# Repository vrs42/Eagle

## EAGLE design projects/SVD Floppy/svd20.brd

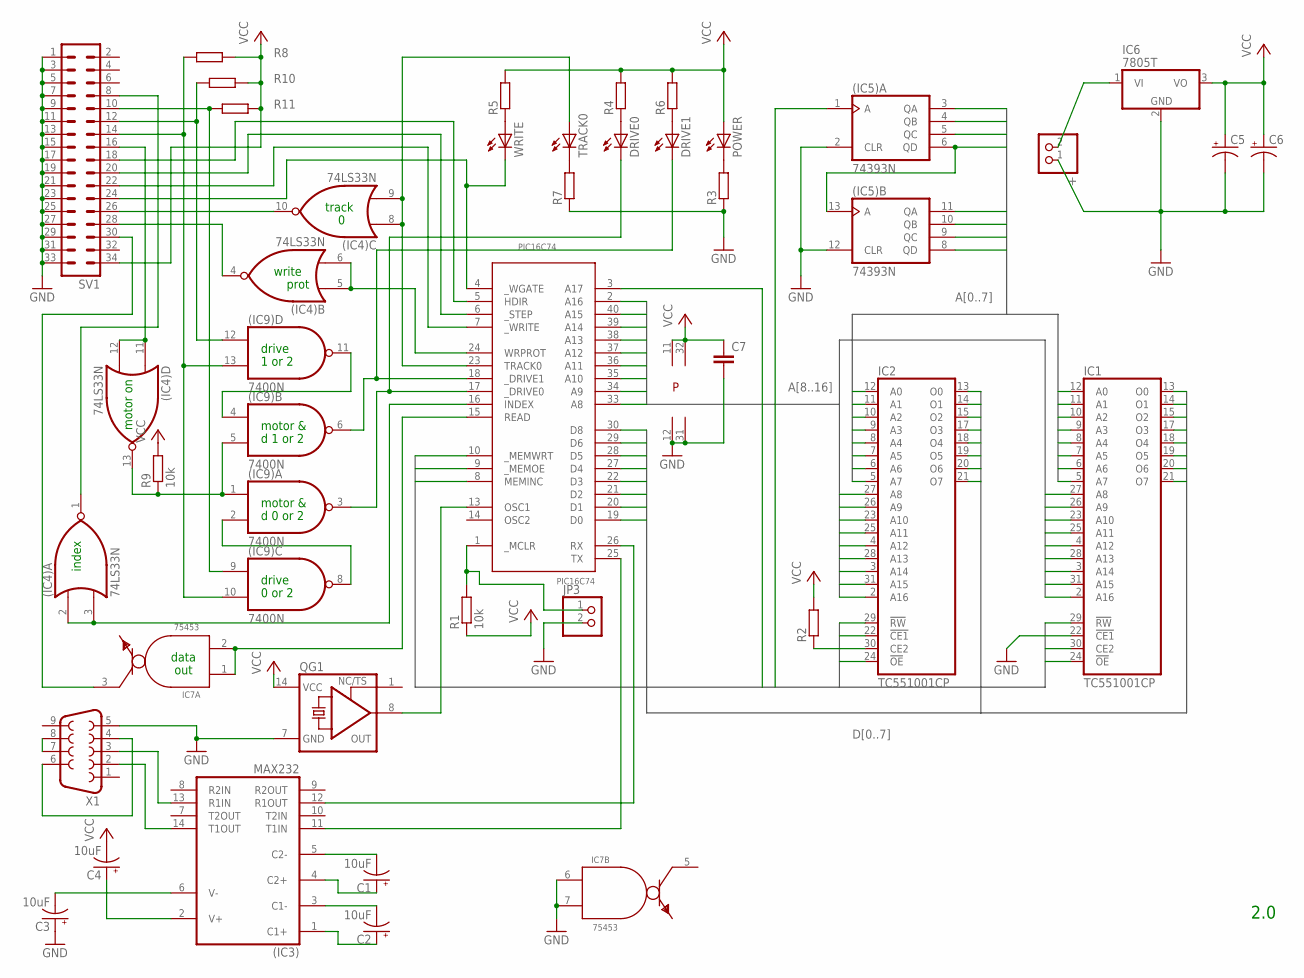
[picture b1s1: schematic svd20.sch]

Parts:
(IC3): MAX232; DIL16
(IC4): 74LS33N; DIL14
(IC5): 74393N; DIL14
(IC9): 7400N; DIL14
+: PINHD-1X2; 1X02
C1, C2, C3, C4: 10uF; E2-5
C5, C6: CPOL-USE2-5; E2-5
C7: C2,5-3; C2.5-3
DRIVE0, DRIVE1: LED3MM
IC1, IC2: TC551001CP; DIL32
IC6: 7805T; TO220H
IC7: 75453; DIL08
JP3: PINHD-1X2; 1X02
PIC16C74: PIC16C74; DIL40
POWER: LED3MM
QG1: XO-14; DIL14S
R1, R9: 10k; 0204/5
R2, R3, R4, R5, R6, R7, R8, R10, R11: R-EU_0204/5; 0204/5
SV1: ML34
TRACK0: LED3MM
WRITE: LED3MM
X1: F09HP

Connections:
!OE: IC1.24 (!OE), IC2.24 (!OE), PIC16C74.9 (_MEMOE)
!WE: IC1.29 (!RW), IC2.29 (!RW), PIC16C74.10 (_MEMWRT)
A0: (IC5).3 (QA), IC1.12 (A0), IC2.12 (A0)
A1: (IC5).4 (QB), IC1.11 (A1), IC2.11 (A1)
A2: (IC5).5 (QC), IC1.10 (A2), IC2.10 (A2)
A3: (IC5).6 (QD), (IC5).13 (A), IC1.9 (A3), IC2.9 (A3)
A4: (IC5).11 (QA), IC1.8 (A4), IC2.8 (A4)
A5: (IC5).10 (QB), IC1.7 (A5), IC2.7 (A5)
A6: (IC5).9 (QC), IC1.6 (A6), IC2.6 (A6)
A7: (IC5).8 (QD), IC1.5 (A7), IC2.5 (A7)
A8: IC1.27 (A8), IC2.27 (A8), PIC16C74.33 (A8)
A9: IC1.26 (A9), IC2.26 (A9), PIC16C74.34 (A9)
A10: IC1.23 (A10), IC2.23 (A10), PIC16C74.35 (A10)
A11: IC1.25 (A11), IC2.25 (A11), PIC16C74.36 (A11)
A12: IC1.4 (A12), IC2.4 (A12), PIC16C74.37 (A12)
A13: IC1.28 (A13), IC2.28 (A13), PIC16C74.38 (A13)
A14: IC1.3 (A14), IC2.3 (A14), PIC16C74.39 (A14)
A15: IC1.31 (A15), IC2.31 (A15), PIC16C74.40 (A15)
A16: IC1.2 (A16), IC2.2 (A16), PIC16C74.2 (A16)
A17: IC1.30 (CE2), IC2.22 (!CE1), PIC16C74.3 (A17)
CLK: (IC5).1 (A), PIC16C74.8 (MEMINC)
D0: IC1.13 (O0), IC2.13 (O0), PIC16C74.19 (D0)
D1: IC1.14 (O1), IC2.14 (O1), PIC16C74.20 (D1)
D2: IC1.15 (O2), IC2.15 (O2), PIC16C74.21 (D2)
D3: IC1.17 (O3), IC2.17 (O3), PIC16C74.22 (D3)
D4: IC1.18 (O4), IC2.18 (O4), PIC16C74.27 (D4)
D5: IC1.19 (O5), IC2.19 (O5), PIC16C74.28 (D5)
D6: IC1.20 (O6), IC2.20 (O6), PIC16C74.29 (D6)
D7: IC1.21 (O7), IC2.21 (O7), PIC16C74.30 (D8)
GND: (IC3).15 (GND), (IC4).7 (GND), (IC5).2 (CLR), (IC5).7 (GND), (IC5).12 (CLR), (IC9).7 (GND), +.1, C3.+, C5.-, C6.-, C7.2, IC1.16 (GND), IC1.22 (!CE1), IC2.16 (GND), IC6.2 (GND), IC7.4 (GND), IC7.6 (I0), IC7.7 (I1), JP3.2, PIC16C74.12 (GND), PIC16C74.31 (GND), QG1.7 (GND), R3.1, R7.1, SV1.1, SV1.3, SV1.5, SV1.7, SV1.9, SV1.11, SV1.13, SV1.15, SV1.17, SV1.19, SV1.21, SV1.23, SV1.25, SV1.27, SV1.29, SV1.31, SV1.33, X1.5
unnamed: IC2.30 (CE2), R2.1
unnamed: JP3.1, PIC16C74.1 (_MCLR), R1.2
unnamed: (IC3).1 (C1+), C2.+
unnamed: (IC3).3 (C1-), C2.-
unnamed: (IC3).4 (C2+), C1.+
unnamed: (IC3).5 (C2-), C1.-
unnamed: (IC3).2 (V+), C4.+
unnamed: PIC16C74.13 (OSC1), QG1.8 (OUT)
unnamed: (IC3).12 (R1OUT), PIC16C74.26 (RX)
unnamed: (IC9).6 (O), DRIVE1.K (C), PIC16C74.18 (_DRIVE1)
unnamed: (IC4).11 (I0), (IC4).12 (I1), SV1.16
unnamed: (IC9).12 (I0), R10.1, SV1.12
unnamed: (IC4).13 (O), (IC9).1 (I0), (IC9).5 (I1), R9.1
unnamed: (IC4).1 (O), SV1.8
unnamed: PIC16C74.4 (_WGATE), SV1.24, WRITE.K (C)
unnamed: PIC16C74.7 (_WRITE), SV1.22
unnamed: (IC4).10 (O), SV1.26
unnamed: X1.7, X1.8
unnamed: IC7.1 (I0), IC7.2 (I1), PIC16C74.15 (READ)
unnamed: (IC9).4 (I0), (IC9).11 (O)
unnamed: (IC4).8 (I0), (IC4).9 (I1), PIC16C74.23 (TRACK0), TRACK0.A
unnamed: (IC9).3 (O), DRIVE0.K (C), PIC16C74.17 (_DRIVE0)
unnamed: (IC3).11 (T1IN), PIC16C74.25 (TX)
unnamed: (IC3).13 (R1IN), X1.3
unnamed: X1.4, X1.6
unnamed: (IC3).14 (T1OUT), X1.2
unnamed: (IC3).6 (V-), C3.-
unnamed: (IC4).2 (I0), (IC4).3 (I1), PIC16C74.16 (INDEX)
unnamed: +.2, IC6.1 (VI)
unnamed: POWER.K (C), R3.2
unnamed: DRIVE0.A, R4.1
unnamed: DRIVE1.A, R6.1
unnamed: R5.1, WRITE.A
unnamed: R7.2, TRACK0.K (C)
unnamed: IC7.3 (O), SV1.30
unnamed: (IC4).5 (I0), (IC4).6 (I1), PIC16C74.24 (WRPROT)
unnamed: (IC9).9 (I0), R11.1, SV1.10
unnamed: (IC9).2 (I1), (IC9).8 (O)
unnamed: (IC4).4 (O), SV1.28
unnamed: PIC16C74.6 (_STEP), SV1.20
unnamed: PIC16C74.5 (HDIR), SV1.18
unnamed: (IC9).10 (I1), (IC9).13 (I1), R8.1, SV1.14
VCC: (IC3).16 (VCC), (IC4).14 (VCC), (IC5).14 (VCC), (IC9).14 (VCC), C4.-, C5.+, C6.+, C7.1, IC1.32 (VCC), IC2.32 (VCC), IC6.3 (VO), IC7.8 (VCC), PIC16C74.11 (VCC), PIC16C74.32 (VCC), POWER.A, QG1.14 (VCC), R1.1, R2.2, R4.2, R5.2, R6.2, R8.2, R9.2, R10.2, R11.2, SV1.34

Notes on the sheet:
2.0
motor on
index
data
out
write
prot
track
drive
motor &
1 or 2
d 1 or 2
d 0 or 2
0 or 2

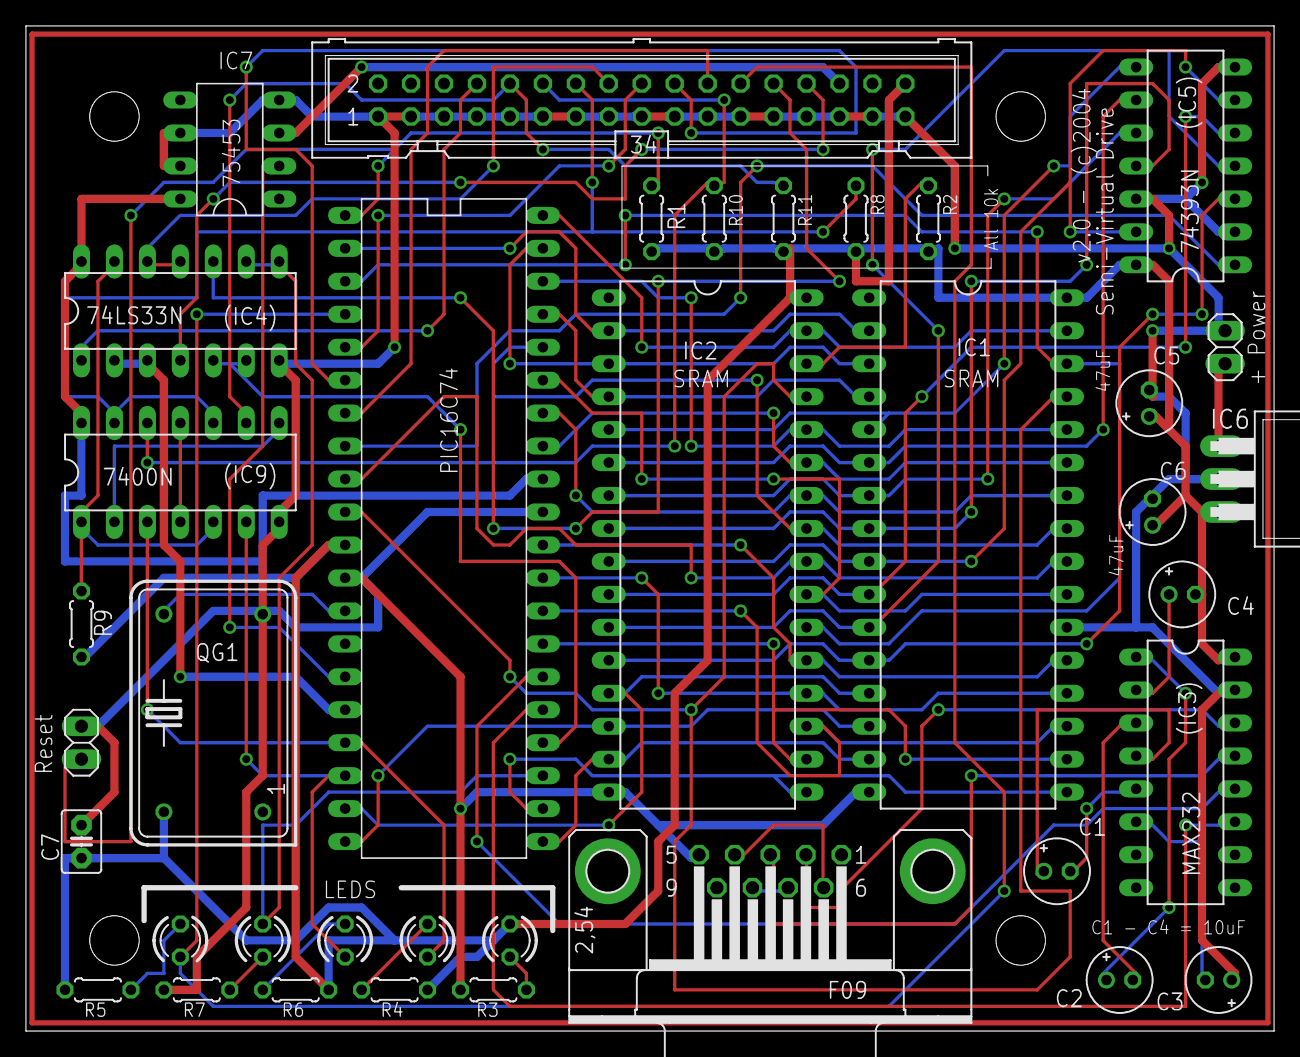
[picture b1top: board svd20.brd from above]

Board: 2 copper layers, 96.2 x 77.5 mm, 37 parts (0 on the bottom side), 73 nets.

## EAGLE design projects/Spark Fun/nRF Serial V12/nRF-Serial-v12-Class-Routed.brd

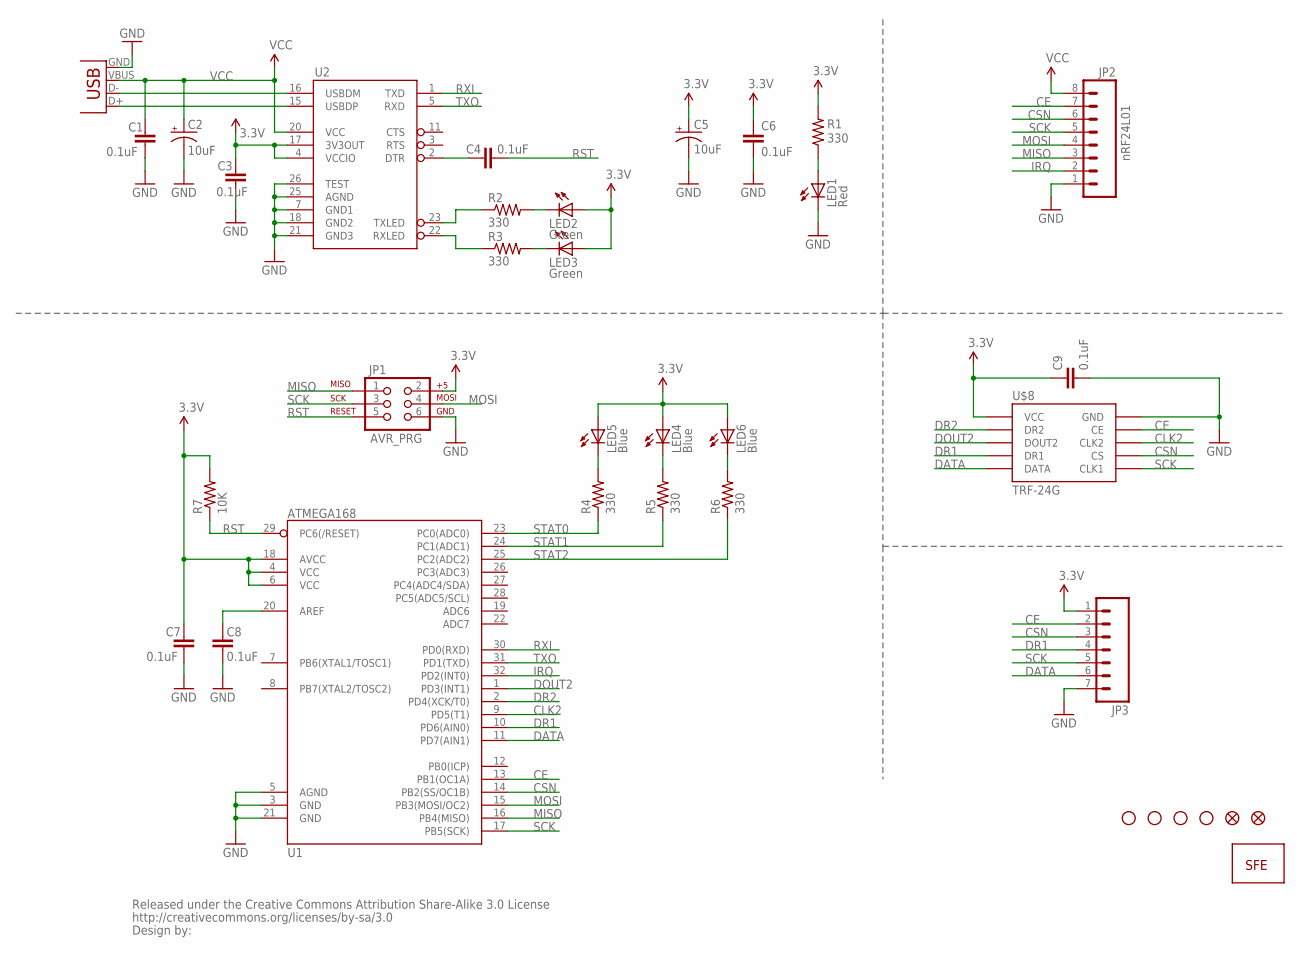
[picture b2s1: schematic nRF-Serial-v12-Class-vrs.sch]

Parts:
C1, C3, C4, C6, C7, C8, C9: 0.1uF; C0402
C2, C5: 10uF; EIA3216
JP1: AVR_PRG; 2X3
JP2: nRF24L01; 1X08
JP3: M07; 1X07
LED1: Red; LED-0603
LED2, LED3: Green; LED-0603
LED4, LED5, LED6: Blue; LED-0603
R1, R2, R3, R4, R5, R6: 330; C0402
R7: 10K; C0402
U1: ATMEGA168; TQFP32-08
U2: FT232RL-BASICSSOP; SSOP28DB
U$1: LOGO-SFENEW; SFE-NEW-WEBLOGO
U$2, U$3: FIDUCIAL1X2; FIDUCIAL-1X2
U$4, U$5, U$6, U$7: STAND-OFF
U$8: TRF-24G; TRF-24G-SOCKET
U$9: CREATIVE_COMMONS
X1: USBSMD; USB-MINIB

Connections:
3.3V: C3.1, C5.A (+), C6.1, C7.1, C9.1, JP1.2, JP3.1, LED2.A, LED3.A, LED4.A, LED5.A, LED6.A, R1.2, R7.2, U1.4 (VCC), U1.6 (VCC), U1.18 (AVCC), U2.4 (VCCIO), U2.17 (3V3OUT), U$8.P$1 (VCC)
CE: JP2.7, JP3.2, U1.13 (PB1(OC1A)), U$8.P$9 (CE)
CLK2: U1.9 (PD5(T1)), U$8.P$8 (CLK2)
CSN: JP2.6, JP3.3, U1.14 (PB2(SS/OC1B)), U$8.P$7 (CS)
DATA: JP3.6, U1.11 (PD7(AIN1)), U$8.P$5 (DATA)
DOUT2: U1.1 (PD3(INT1)), U$8.P$3 (DOUT2)
DR1: JP3.4, U1.10 (PD6(AIN0)), U$8.P$4 (DR1)
DR2: U1.2 (PD4(XCK/T0)), U$8.P$2 (DR2)
GND: C1.2, C2.C (-), C3.2, C5.C (-), C6.2, C7.2, C8.1, C9.2, JP1.6, JP2.1, JP3.7, LED1.C, U1.3 (GND), U1.5 (AGND), U1.21 (GND), U2.7 (GND1), U2.18 (GND2), U2.21 (GND3), U2.25 (AGND), U2.26 (TEST), U$8.P$10 (GND), X1.GND
IRQ: JP2.2, U1.32 (PD2(INT0))
MISO: JP1.1, JP2.3, U1.16 (PB4(MISO))
MOSI: JP1.4, JP2.4, U1.15 (PB3(MOSI/OC2))
unnamed: C8.2, U1.20 (AREF)
unnamed: C4.2, U2.2 (DTR)
unnamed: R2.1, U2.23 (TXLED)
unnamed: R3.1, U2.22 (RXLED)
unnamed: LED3.C, R3.2
unnamed: LED2.C, R2.2
unnamed: LED5.C, R4.2
unnamed: LED4.C, R5.2
unnamed: LED6.C, R6.2
unnamed: LED1.A, R1.1
unnamed: U2.16 (USBDM), X1.D-
unnamed: U2.15 (USBDP), X1.D+
RST: C4.1, JP1.5, R7.1, U1.29 (PC6(/RESET))
RXI: U1.30 (PD0(RXD)), U2.1 (TXD)
SCK: JP1.3, JP2.5, JP3.5, U1.17 (PB5(SCK)), U$8.P$6 (CLK1)
STAT0: R4.1, U1.23 (PC0(ADC0))
STAT1: R5.1, U1.24 (PC1(ADC1))
STAT2: R6.1, U1.25 (PC2(ADC2))
TXO: U1.31 (PD1(TXD)), U2.5 (RXD)
VCC: C1.1, C2.A (+), JP2.8, U2.20 (VCC), X1.VBUS

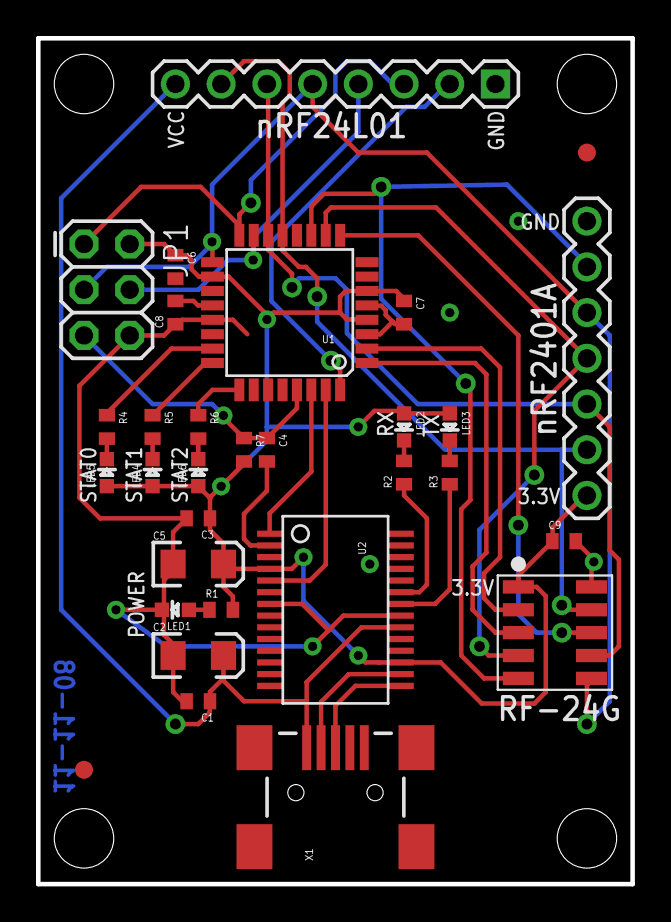
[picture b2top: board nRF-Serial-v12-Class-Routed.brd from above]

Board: 2 copper layers, 33.0 x 47.0 mm, 37 parts (1 on the bottom side), 32 nets.

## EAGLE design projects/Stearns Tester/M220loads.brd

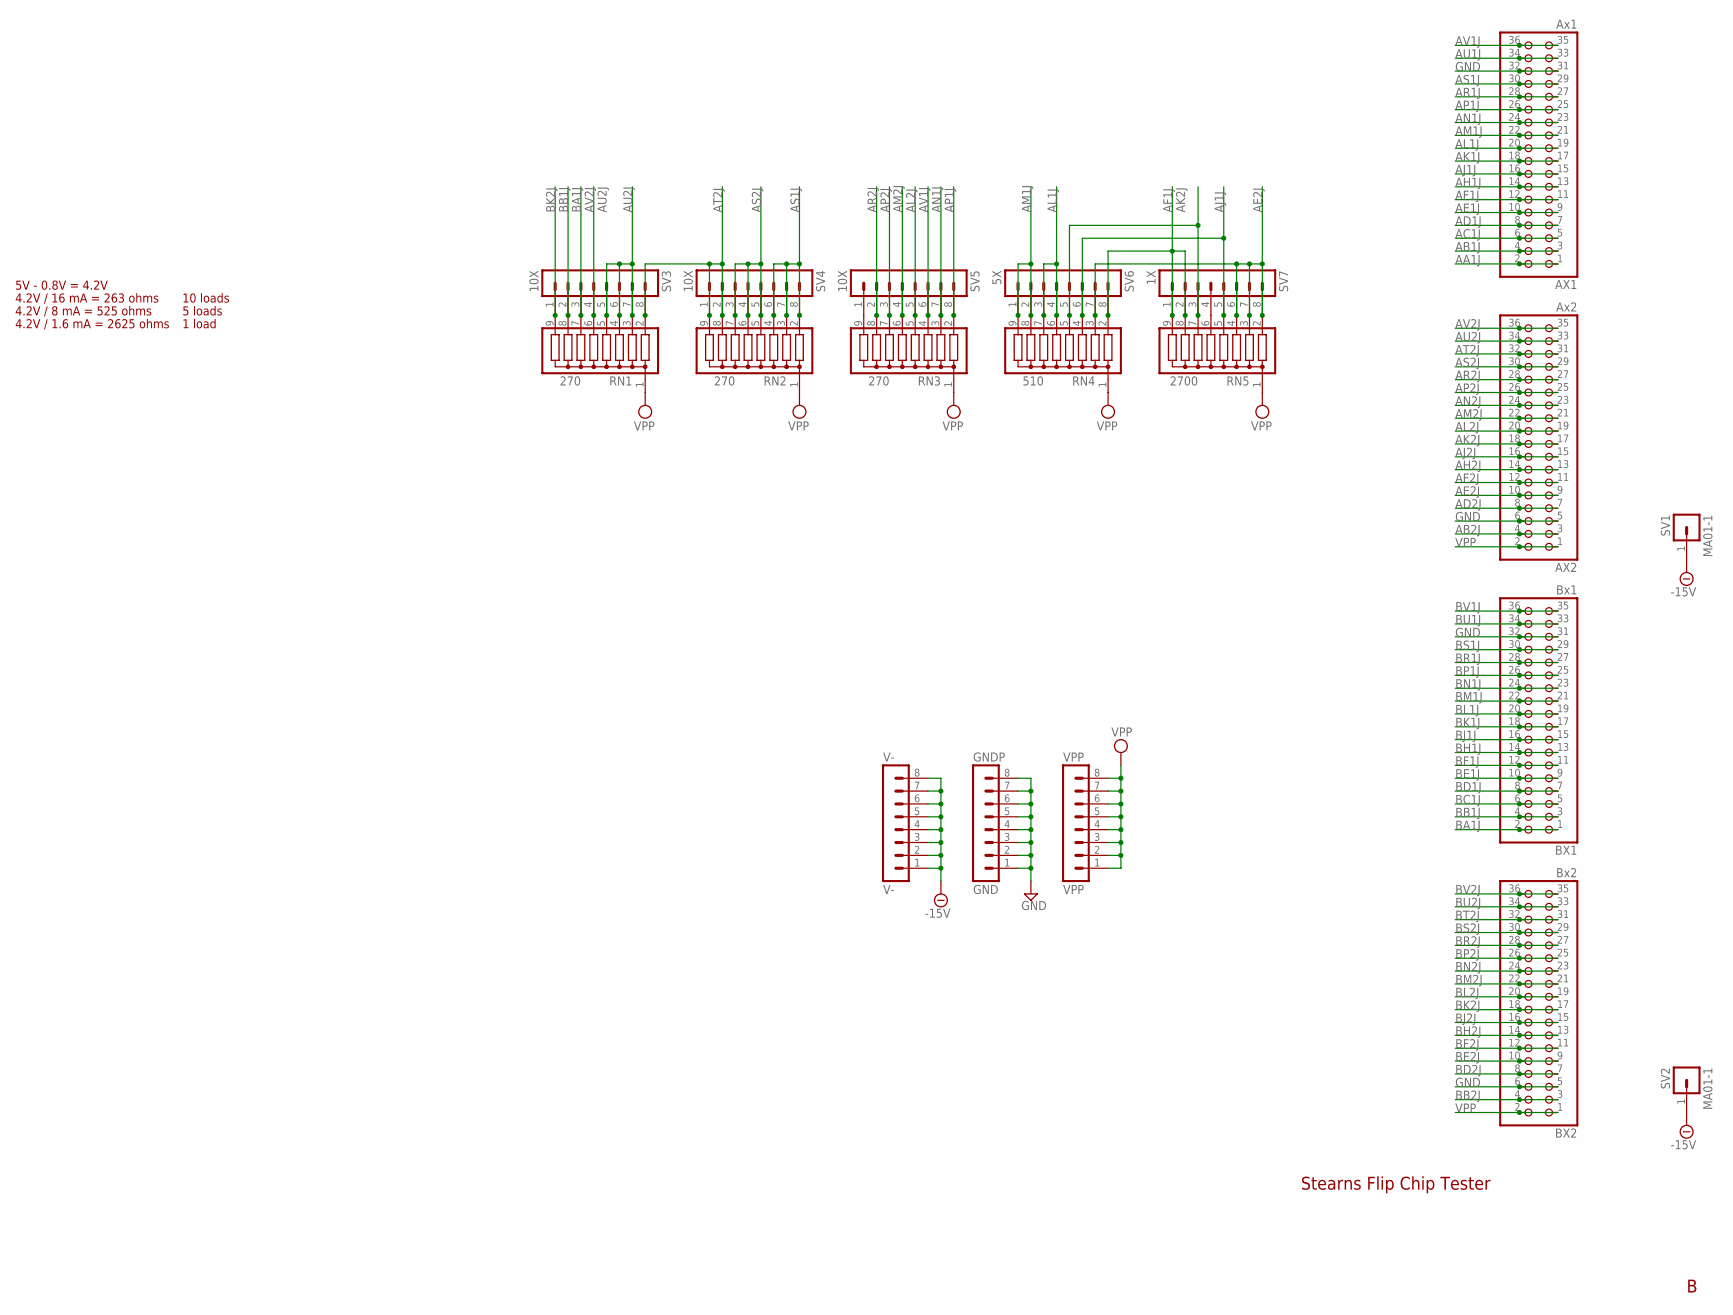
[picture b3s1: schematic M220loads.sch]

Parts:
AX1: Ax1; 2X18
AX2: Ax2; 2X18
BX1: Bx1; 2X18
BX2: Bx2; 2X18
GNDP: GND; MA08-1
RN1, RN2, RN3: 270; SIL9
RN4: 510; SIL9
RN5: 2700; SIL9
SV1, SV2: MA01-1
SV3, SV4, SV5: 10X; MA08-1
SV6: 5X; MA08-1
SV7: 1X; MA08-1
V-: V-; MA08-1
VPP: VPP; MA08-1

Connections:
-15V: SV1.1, SV2.1, V-.1, V-.2, V-.3, V-.4, V-.5, V-.6, V-.7, V-.8
AA1J: AX1.1, AX1.2
AB1J: AX1.3, AX1.4
AB2J: AX2.3, AX2.4
AC1J: AX1.5, AX1.6
AD1J: AX1.7, AX1.8
AD2J: AX2.7, AX2.8
AE1J: AX1.9, AX1.10
AE2J: AX2.9, AX2.10, RN4.3, RN5.2, RN5.3, RN5.4, SV6.7, SV7.6, SV7.7, SV7.8
AF1J: AX1.11, AX1.12, RN4.2, RN5.8, RN5.9, SV6.8, SV7.1, SV7.2
AF2J: AX2.11, AX2.12
AH1J: AX1.13, AX1.14
AH2J: AX2.13, AX2.14
AJ1J: AX1.15, AX1.16, RN4.4, RN5.5, SV6.6, SV7.5
AJ2J: AX2.15, AX2.16
AK1J: AX1.17, AX1.18
AK2J: AX2.17, AX2.18, RN4.5, RN5.7, SV6.5, SV7.3
AL1J: AX1.19, AX1.20, RN4.6, RN4.7, SV6.3, SV6.4
AL2J: AX2.19, AX2.20, RN3.5, SV5.5
AM1J: AX1.21, AX1.22, RN4.8, RN4.9, SV6.1, SV6.2
AM2J: AX2.21, AX2.22, RN3.6, SV5.4
AN1J: AX1.23, AX1.24, RN3.3, SV5.7
AN2J: AX2.23, AX2.24
AP1J: AX1.25, AX1.26, RN3.2, SV5.8
AP2J: AX2.25, AX2.26, RN3.7, SV5.3
AR1J: AX1.27, AX1.28
AR2J: AX2.27, AX2.28, RN3.8, SV5.2
AS1J: AX1.29, AX1.30, RN2.2, RN2.3, RN2.4, SV4.6, SV4.7, SV4.8
AS2J: AX2.29, AX2.30, RN2.5, RN2.6, RN2.7, SV4.3, SV4.4, SV4.5
AT2J: AX2.31, AX2.32, RN1.2, RN2.8, RN2.9, SV3.8, SV4.1, SV4.2
AU1J: AX1.33, AX1.34
AU2J: AX2.33, AX2.34, RN1.3, RN1.4, RN1.5, SV3.5, SV3.6, SV3.7
AV1J: AX1.35, AX1.36, RN3.4, SV5.6
AV2J: AX2.35, AX2.36, RN1.6, SV3.4
BA1J: BX1.1, BX1.2, RN1.7, SV3.3
BB1J: BX1.3, BX1.4, RN1.8, SV3.2
BB2J: BX2.3, BX2.4
BC1J: BX1.5, BX1.6
BD1J: BX1.7, BX1.8
BD2J: BX2.7, BX2.8
BE1J: BX1.9, BX1.10
BE2J: BX2.9, BX2.10
BF1J: BX1.11, BX1.12
BF2J: BX2.11, BX2.12
BH1J: BX1.13, BX1.14
BH2J: BX2.13, BX2.14
BJ1J: BX1.15, BX1.16
BJ2J: BX2.15, BX2.16
BK1J: BX1.17, BX1.18
BK2J: BX2.17, BX2.18, RN1.9, SV3.1
BL1J: BX1.19, BX1.20
BL2J: BX2.19, BX2.20
BM1J: BX1.21, BX1.22
BM2J: BX2.21, BX2.22
BN1J: BX1.23, BX1.24
BN2J: BX2.23, BX2.24
BP1J: BX1.25, BX1.26
BP2J: BX2.25, BX2.26
BR1J: BX1.27, BX1.28
BR2J: BX2.27, BX2.28
BS1J: BX1.29, BX1.30
BS2J: BX2.29, BX2.30
BT2J: BX2.31, BX2.32
BU1J: BX1.33, BX1.34
BU2J: BX2.33, BX2.34
BV1J: BX1.35, BX1.36
BV2J: BX2.35, BX2.36
GND: AX1.31, AX1.32, AX2.5, AX2.6, BX1.31, BX1.32, BX2.5, BX2.6, GNDP.1, GNDP.2, GNDP.3, GNDP.4, GNDP.5, GNDP.6, GNDP.7, GNDP.8
unnamed: RN3.9, SV5.1
unnamed: RN5.6, SV7.4
VPP: AX2.1, AX2.2, BX2.1, BX2.2, RN1.1, RN2.1, RN3.1, RN4.1, RN5.1, VPP.1, VPP.2, VPP.3, VPP.4, VPP.5, VPP.6, VPP.7, VPP.8

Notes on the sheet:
Stearns Flip Chip Tester
5V - 0.8V = 4.2V
4.2V / 16 mA = 263 ohms
4.2V / 8 mA = 525 ohms
4.2V / 1.6 mA = 2625 ohms
10 loads
5 loads
1 load

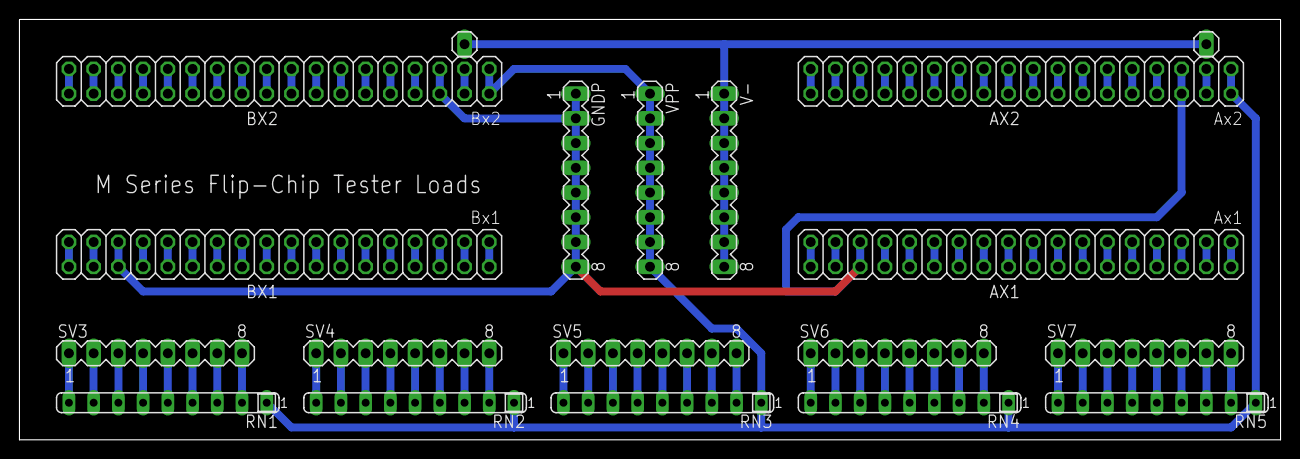
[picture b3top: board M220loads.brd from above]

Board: 4 copper layers, 129.5 x 43.2 mm, 19 parts (0 on the bottom side), 71 nets.

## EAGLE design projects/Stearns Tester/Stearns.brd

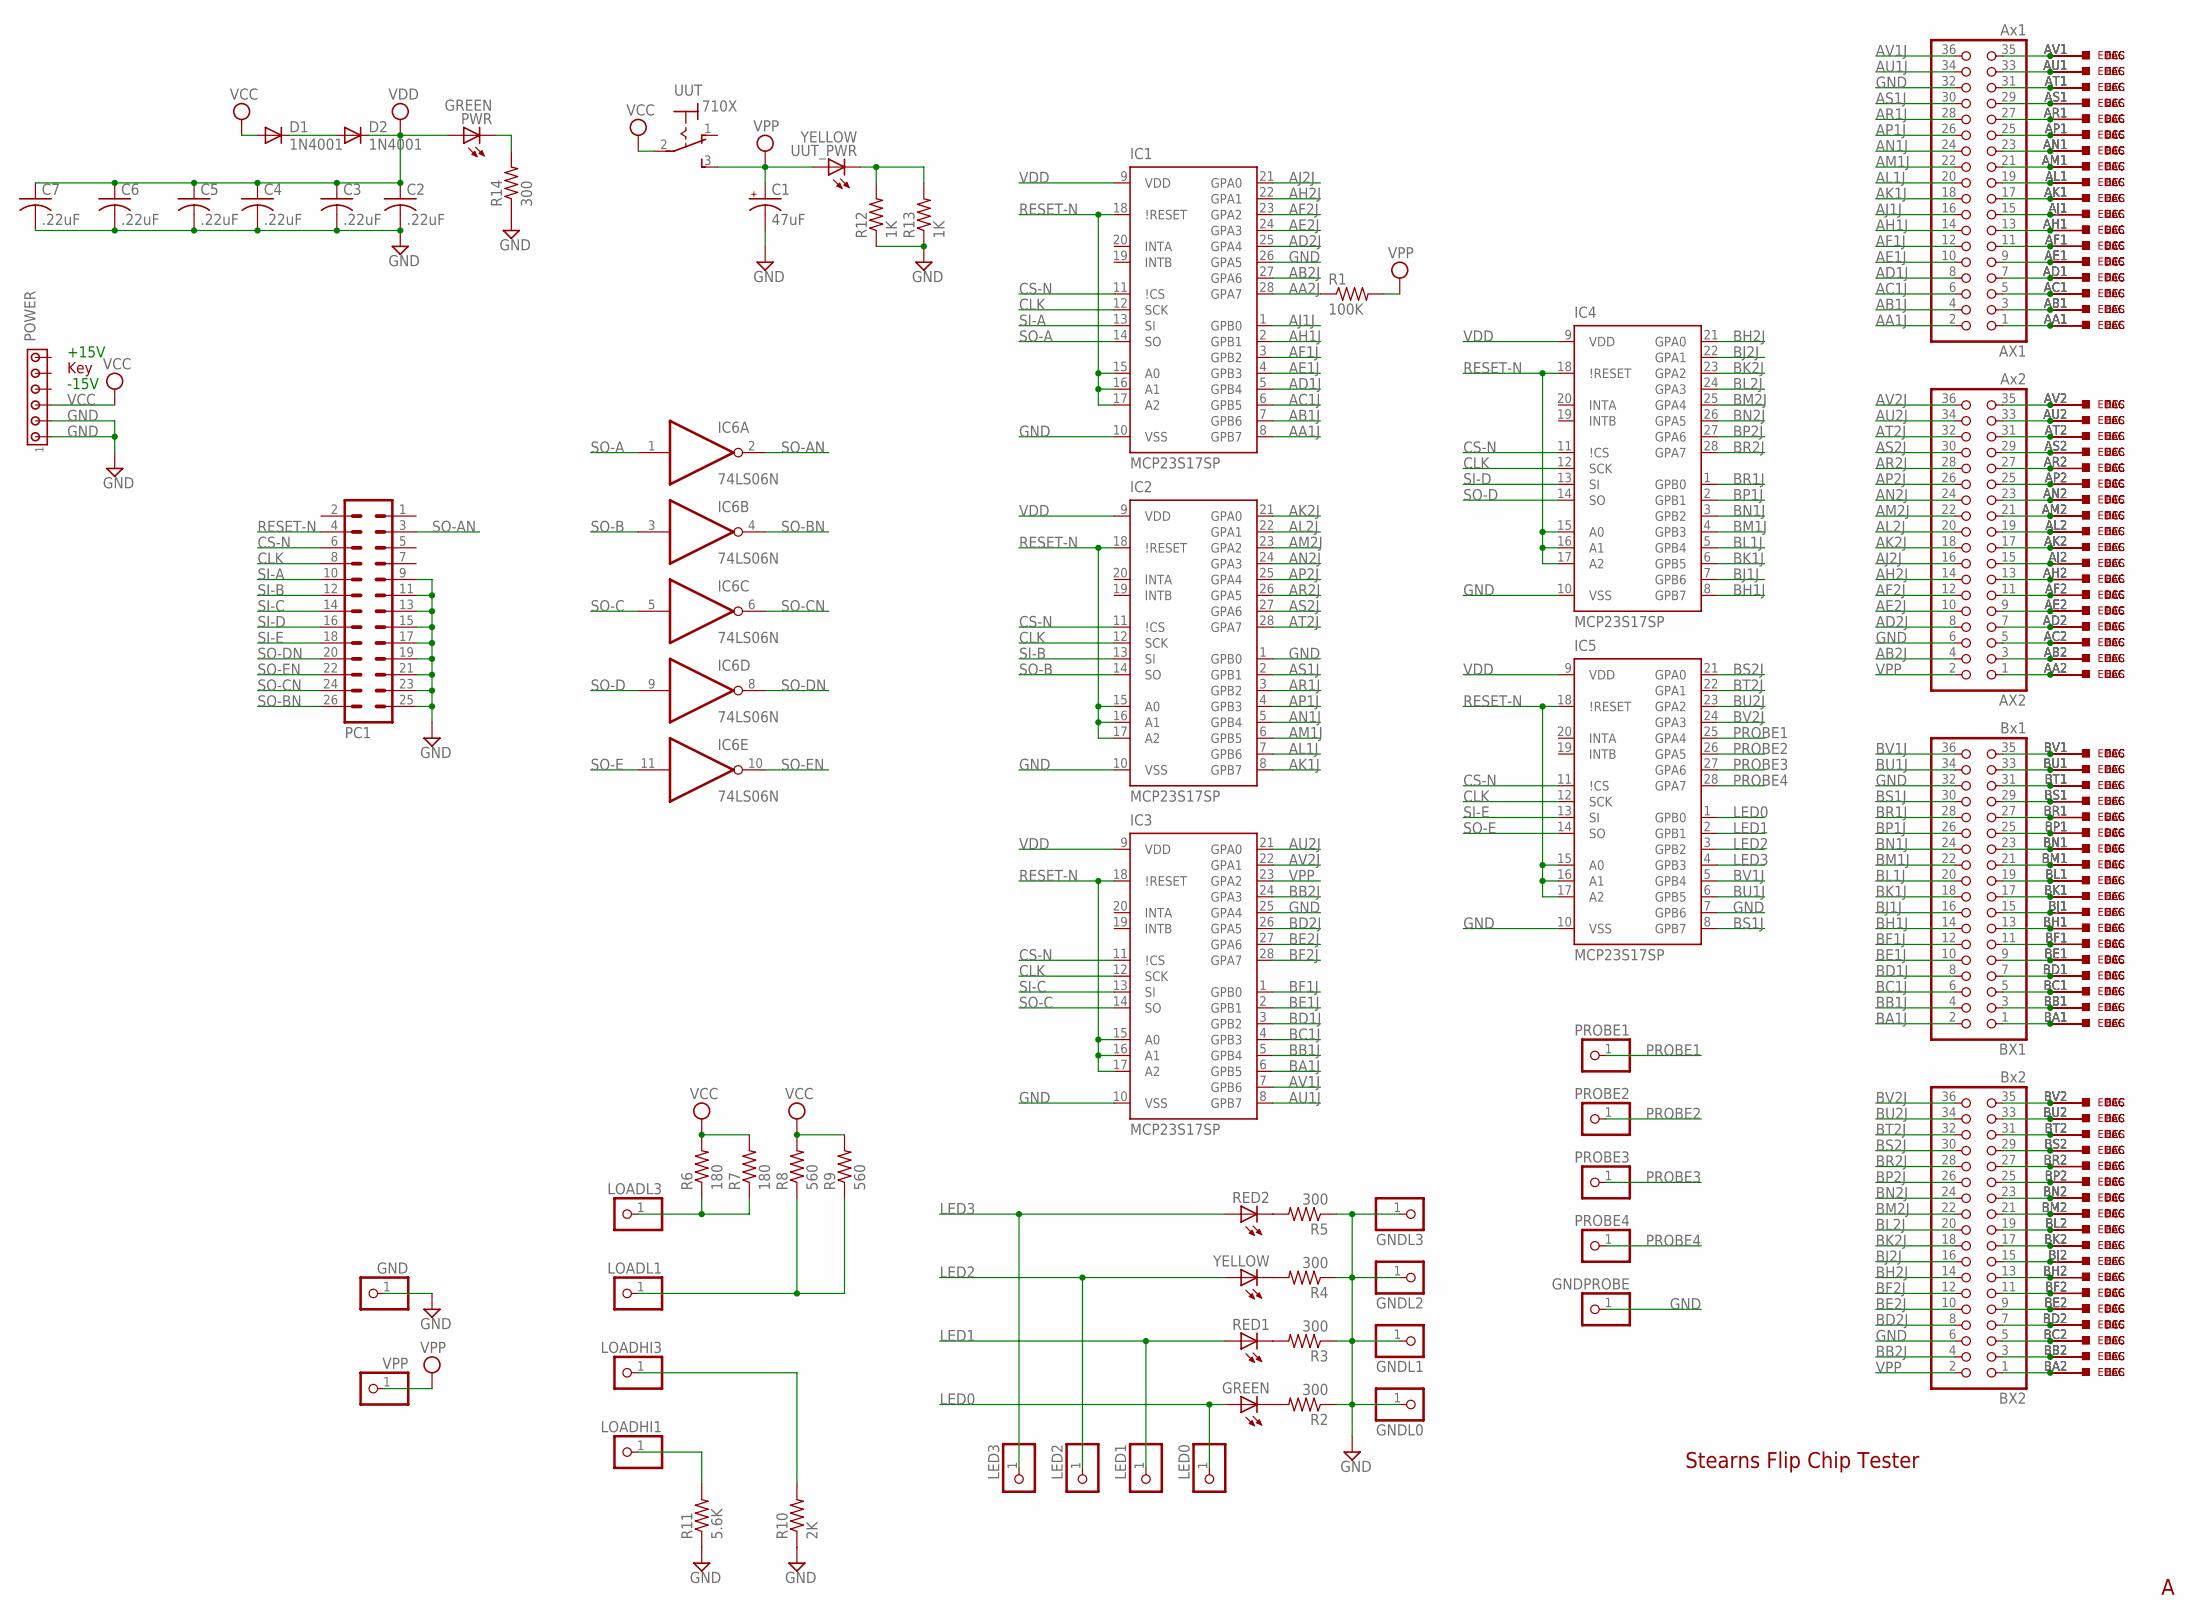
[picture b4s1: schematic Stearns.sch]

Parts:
AX1: Ax1; 2X18
AX2: Ax2; 2X18
BX1: Bx1; 2X18
BX2: Bx2; 2X18
C1: 47uF; E5-8,5
C2, C3, C4, C5, C6, C7: .22uF; C050-025X075
D1, D2: 1N4001; DO41-10
DEC: W971; H807-2
ECS: W971ECS; ECS2418-2
EDAC: W971EDAC; EDAC346-36-2
GND: PINHD-1X1; 1X01
GNDL0, GNDL1, GNDL2, GNDL3: PINHD-1X1; 1X01
GNDPROBE: PINHD-1X1; 1X01
GREEN: LED5MM
IC1, IC2, IC3, IC4, IC5: MCP23S17SP; DIL28-3
IC6: 74LS06N; DIL14
LED0, LED1, LED2, LED3: PINHD-1X1; 1X01
LOADHI1, LOADHI3: PINHD-1X1; 1X01
LOADL1, LOADL3: PINHD-1X1; 1X01
PC1: MA13-2
POWER: MTA06-156; 1X6MTA
PROBE1, PROBE2, PROBE3, PROBE4: PINHD-1X1; 1X01
PWR: GREEN; LED5MM
R1: 100K; 0207/10
R2, R3, R4, R5, R14: 300; 0207/10
R6, R7: 180; 0207/10
R8, R9: 560; 0207/10
R10: 2K; 0207/10
R11: 5.6K; 0207/10
R12, R13: 1K; 0207/10
RED1, RED2: LED5MM
UUT: 710X; 7109MD9V3
UUT_PWR: YELLOW; LED5MM
VPP: PINHD-1X1; 1X01
YELLOW: LED5MM

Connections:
AA1J: AX1.2, IC1.8 (GPB7)
AA2J: IC1.28 (GPA7), R1.1
AB1J: AX1.4, IC1.7 (GPB6)
AB2J: AX2.4, IC1.27 (GPA6)
AC1J: AX1.6, IC1.6 (GPB5)
AD1J: AX1.8, IC1.5 (GPB4)
AD2J: AX2.8, IC1.25 (GPA4)
AE1J: AX1.10, IC1.4 (GPB3)
AE2J: AX2.10, IC1.24 (GPA3)
AF1J: AX1.12, IC1.3 (GPB2)
AF2J: AX2.12, IC1.23 (GPA2)
AH1J: AX1.14, IC1.2 (GPB1)
AH2J: AX2.14, IC1.22 (GPA1)
AJ1J: AX1.16, IC1.1 (GPB0)
AJ2J: AX2.16, IC1.21 (GPA0)
AK1J: AX1.18, IC2.8 (GPB7)
AK2J: AX2.18, IC2.21 (GPA0)
AL1J: AX1.20, IC2.7 (GPB6)
AL2J: AX2.20, IC2.22 (GPA1)
AM1J: AX1.22, IC2.6 (GPB5)
AM2J: AX2.22, IC2.23 (GPA2)
AN1J: AX1.24, IC2.5 (GPB4)
AN2J: AX2.24, IC2.24 (GPA3)
AP1J: AX1.26, IC2.4 (GPB3)
AP2J: AX2.26, IC2.25 (GPA4)
AR1J: AX1.28, IC2.3 (GPB2)
AR2J: AX2.28, IC2.26 (GPA5)
AS1J: AX1.30, IC2.2 (GPB1)
AS2J: AX2.30, IC2.27 (GPA6)
AT2J: AX2.32, IC2.28 (GPA7)
AU1J: AX1.34, IC3.8 (GPB7)
AU2J: AX2.34, IC3.21 (GPA0)
AV1J: AX1.36, IC3.7 (GPB6)
AV2J: AX2.36, IC3.22 (GPA1)
BA1J: BX1.2, IC3.6 (GPB5)
BB1J: BX1.4, IC3.5 (GPB4)
BB2J: BX2.4, IC3.24 (GPA3)
BC1J: BX1.6, IC3.4 (GPB3)
BD1J: BX1.8, IC3.3 (GPB2)
BD2J: BX2.8, IC3.26 (GPA5)
BE1J: BX1.10, IC3.2 (GPB1)
BE2J: BX2.10, IC3.27 (GPA6)
BF1J: BX1.12, IC3.1 (GPB0)
BF2J: BX2.12, IC3.28 (GPA7)
BH1J: BX1.14, IC4.8 (GPB7)
BH2J: BX2.14, IC4.21 (GPA0)
BJ1J: BX1.16, IC4.7 (GPB6)
BJ2J: BX2.16, IC4.22 (GPA1)
BK1J: BX1.18, IC4.6 (GPB5)
BK2J: BX2.18, IC4.23 (GPA2)
BL1J: BX1.20, IC4.5 (GPB4)
BL2J: BX2.20, IC4.24 (GPA3)
BM1J: BX1.22, IC4.4 (GPB3)
BM2J: BX2.22, IC4.25 (GPA4)
BN1J: BX1.24, IC4.3 (GPB2)
BN2J: BX2.24, IC4.26 (GPA5)
BP1J: BX1.26, IC4.2 (GPB1)
BP2J: BX2.26, IC4.27 (GPA6)
BR1J: BX1.28, IC4.1 (GPB0)
BR2J: BX2.28, IC4.28 (GPA7)
BS1J: BX1.30, IC5.8 (GPB7)
BS2J: BX2.30, IC5.21 (GPA0)
BT2J: BX2.32, IC5.22 (GPA1)
BU1J: BX1.34, IC5.6 (GPB5)
BU2J: BX2.34, IC5.23 (GPA2)
BV1J: BX1.36, IC5.5 (GPB4)
BV2J: BX2.36, IC5.24 (GPA3)
CLK: IC1.12 (SCK), IC2.12 (SCK), IC3.12 (SCK), IC4.12 (SCK), IC5.12 (SCK), PC1.8
CS-N: IC1.11 (\!CS), IC2.11 (\!CS), IC3.11 (\!CS), IC4.11 (\!CS), IC5.11 (\!CS), PC1.6
GND: AX1.32, AX2.6, BX1.32, BX2.6, C1.-, C2.2, C3.2, C4.2, C5.2, C6.2, C7.2, GND.1, GNDL0.1, GNDL1.1, GNDL2.1, GNDL3.1, GNDPROBE.1, IC1.10 (VSS), IC1.26 (GPA5), IC2.1 (GPB0), IC2.10 (VSS), IC3.10 (VSS), IC3.25 (GPA4), IC4.10 (VSS), IC5.7 (GPB6), IC5.10 (VSS), IC6.7 (GND), PC1.9, PC1.11, PC1.13, PC1.15, PC1.17, PC1.19, PC1.21, PC1.23, PC1.25, POWER.1, POWER.2, R2.1, R3.1, R4.1, R5.1, R10.1, R11.1, R12.1, R13.1, R14.1, UUT.NC@1 (GND), UUT.NC@2 (GND), UUT.NC@3 (GND), UUT.NC@4 (GND), UUT.NC@5 (GND), UUT.NC@6 (GND), UUT.NC@7 (GND), UUT.NC@8 (GND)
LED0: GREEN.A, IC5.1 (GPB0), LED0.1
LED1: IC5.2 (GPB1), LED1.1, RED1.A
LED2: IC5.3 (GPB2), LED2.1, YELLOW.A
LED3: IC5.4 (GPB3), LED3.1, RED2.A
unnamed: AX1.1, DEC.AA1, ECS.AA1, EDAC.AA1
unnamed: AX1.35, DEC.AV1, ECS.AV1, EDAC.AV1
unnamed: AX1.33, DEC.AU1, ECS.AU1, EDAC.AU1
unnamed: AX1.31, DEC.AT1, ECS.AT1, EDAC.AT1
unnamed: AX1.29, DEC.AS1, ECS.AS1, EDAC.AS1
unnamed: AX1.27, DEC.AR1, ECS.AR1, EDAC.AR1
unnamed: AX1.25, DEC.AP1, ECS.AP1, EDAC.AP1
unnamed: AX1.23, DEC.AN1, ECS.AN1, EDAC.AN1
unnamed: AX1.21, DEC.AM1, ECS.AM1, EDAC.AM1
unnamed: AX1.19, DEC.AL1, ECS.AL1, EDAC.AL1
unnamed: AX1.17, DEC.AK1, ECS.AK1, EDAC.AK1
unnamed: AX1.15, DEC.AJ1, ECS.AJ1, EDAC.AJ1
unnamed: AX1.13, DEC.AH1, ECS.AH1, EDAC.AH1
unnamed: AX1.11, DEC.AF1, ECS.AF1, EDAC.AF1
unnamed: AX1.9, DEC.AE1, ECS.AE1, EDAC.AE1
unnamed: AX1.7, DEC.AD1, ECS.AD1, EDAC.AD1
unnamed: AX1.5, DEC.AC1, ECS.AC1, EDAC.AC1
unnamed: AX1.3, DEC.AB1, ECS.AB1, EDAC.AB1
unnamed: AX2.1, DEC.AA2, ECS.AA2, EDAC.AA2
unnamed: AX2.3, DEC.AB2, ECS.AB2, EDAC.AB2
unnamed: AX2.5, DEC.AC2, ECS.AC2, EDAC.AC2
unnamed: AX2.7, DEC.AD2, ECS.AD2, EDAC.AD2
unnamed: AX2.9, DEC.AE2, ECS.AE2, EDAC.AE2
unnamed: AX2.11, DEC.AF2, ECS.AF2, EDAC.AF2
unnamed: AX2.13, DEC.AH2, ECS.AH2, EDAC.AH2
unnamed: AX2.15, DEC.AJ2, ECS.AJ2, EDAC.AJ2
unnamed: AX2.17, DEC.AK2, ECS.AK2, EDAC.AK2
unnamed: AX2.19, DEC.AL2, ECS.AL2, EDAC.AL2
unnamed: AX2.21, DEC.AM2, ECS.AM2, EDAC.AM2
unnamed: AX2.23, DEC.AN2, ECS.AN2, EDAC.AN2
unnamed: AX2.25, DEC.AP2, ECS.AP2, EDAC.AP2
unnamed: AX2.27, DEC.AR2, ECS.AR2, EDAC.AR2
unnamed: AX2.29, DEC.AS2, ECS.AS2, EDAC.AS2
unnamed: AX2.31, DEC.AT2, ECS.AT2, EDAC.AT2
unnamed: AX2.33, DEC.AU2, ECS.AU2, EDAC.AU2
unnamed: AX2.35, DEC.AV2, ECS.AV2, EDAC.AV2
unnamed: BX2.1, DEC.BA2, ECS.BA2, EDAC.BA2
unnamed: BX2.3, DEC.BB2, ECS.BB2, EDAC.BB2
unnamed: BX2.5, DEC.BC2, ECS.BC2, EDAC.BC2
unnamed: BX2.7, DEC.BD2, ECS.BD2, EDAC.BD2
unnamed: BX2.9, DEC.BE2, ECS.BE2, EDAC.BE2
unnamed: BX2.11, DEC.BF2, ECS.BF2, EDAC.BF2
unnamed: BX2.13, DEC.BH2, ECS.BH2, EDAC.BH2
unnamed: BX2.15, DEC.BJ2, ECS.BJ2, EDAC.BJ2
unnamed: BX2.17, DEC.BK2, ECS.BK2, EDAC.BK2
unnamed: BX2.19, DEC.BL2, ECS.BL2, EDAC.BL2
unnamed: BX2.21, DEC.BM2, ECS.BM2, EDAC.BM2
unnamed: BX2.23, DEC.BN2, ECS.BN2, EDAC.BN2
unnamed: BX2.25, DEC.BP2, ECS.BP2, EDAC.BP2
unnamed: BX2.27, DEC.BR2, ECS.BR2, EDAC.BR2
unnamed: BX2.29, DEC.BS2, ECS.BS2, EDAC.BS2
unnamed: BX2.31, DEC.BT2, ECS.BT2, EDAC.BT2
unnamed: BX2.33, DEC.BU2, ECS.BU2, EDAC.BU2
unnamed: BX2.35, DEC.BV2, ECS.BV2, EDAC.BV2
unnamed: BX1.1, DEC.BA1, ECS.BA1, EDAC.BA1
unnamed: BX1.3, DEC.BB1, ECS.BB1, EDAC.BB1
unnamed: BX1.5, DEC.BC1, ECS.BC1, EDAC.BC1
unnamed: BX1.7, DEC.BD1, ECS.BD1, EDAC.BD1
unnamed: BX1.9, DEC.BE1, ECS.BE1, EDAC.BE1
unnamed: BX1.11, DEC.BF1, ECS.BF1, EDAC.BF1
unnamed: BX1.13, DEC.BH1, ECS.BH1, EDAC.BH1
unnamed: BX1.15, DEC.BJ1, ECS.BJ1, EDAC.BJ1
unnamed: BX1.17, DEC.BK1, ECS.BK1, EDAC.BK1
unnamed: BX1.19, DEC.BL1, ECS.BL1, EDAC.BL1
unnamed: BX1.21, DEC.BM1, ECS.BM1, EDAC.BM1
unnamed: BX1.23, DEC.BN1, ECS.BN1, EDAC.BN1
unnamed: BX1.25, DEC.BP1, ECS.BP1, EDAC.BP1
unnamed: BX1.27, DEC.BR1, ECS.BR1, EDAC.BR1
unnamed: BX1.29, DEC.BS1, ECS.BS1, EDAC.BS1
unnamed: BX1.31, DEC.BT1, ECS.BT1, EDAC.BT1
unnamed: BX1.33, DEC.BU1, ECS.BU1, EDAC.BU1
unnamed: BX1.35, DEC.BV1, ECS.BV1, EDAC.BV1
unnamed: GREEN.K (C), R2.2
unnamed: R3.2, RED1.K (C)
unnamed: R4.2, YELLOW.K (C)
unnamed: R5.2, RED2.K (C)
unnamed: LOADL3.1, R6.1, R7.1
unnamed: LOADL1.1, R8.1, R9.1
unnamed: LOADHI1.1, R11.2
unnamed: LOADHI3.1, R10.2
unnamed: D1.C, D2.A
unnamed: R12.2, R13.2, UUT_PWR.K (C)
unnamed: PWR.K (C), R14.2
PROBE1: IC5.25 (GPA4), PROBE1.1
PROBE2: IC5.26 (GPA5), PROBE2.1
PROBE3: IC5.27 (GPA6), PROBE3.1
PROBE4: IC5.28 (GPA7), PROBE4.1
RESET-N: IC1.15 (A0), IC1.16 (A1), IC1.17 (A2), IC1.18 (\!RESET), IC2.15 (A0), IC2.16 (A1), IC2.17 (A2), IC2.18 (\!RESET), IC3.15 (A0), IC3.16 (A1), IC3.17 (A2), IC3.18 (\!RESET), IC4.15 (A0), IC4.16 (A1), IC4.17 (A2), IC4.18 (\!RESET), IC5.15 (A0), IC5.16 (A1), IC5.17 (A2), IC5.18 (\!RESET), PC1.4
SI-A: IC1.13 (SI), PC1.10
SI-B: IC2.13 (SI), PC1.12
SI-C: IC3.13 (SI), PC1.14
SI-D: IC4.13 (SI), PC1.16
SI-E: IC5.13 (SI), PC1.18
SO-A: IC1.14 (SO), IC6.1 (I)
SO-AN: IC6.2 (O), PC1.3
SO-B: IC2.14 (SO), IC6.3 (I)
SO-BN: IC6.4 (O), PC1.26
SO-C: IC3.14 (SO), IC6.5 (I)
SO-CN: IC6.6 (O), PC1.24
SO-D: IC4.14 (SO), IC6.9 (I)
SO-DN: IC6.8 (O), PC1.20
SO-E: IC5.14 (SO), IC6.11 (I)
SO-EN: IC6.10 (O), PC1.22
VCC: D1.A, IC6.14 (VCC), POWER.3, R6.2, R7.2, R8.2, R9.2, UUT.2
VDD: C2.1, C3.1, C4.1, C5.1, C6.1, C7.1, D2.C, IC1.9 (VDD), IC2.9 (VDD), IC3.9 (VDD), IC4.9 (VDD), IC5.9 (VDD), PWR.A
VPP: AX2.2, BX2.2, C1.+, IC3.23 (GPA2), R1.2, UUT.3 (S), UUT_PWR.A, VPP.1

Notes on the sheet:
Stearns Flip Chip Tester
-15V
+15V
Key

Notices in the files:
projects/SVD Floppy/svd20.brd:
v2.0 - (c)2004
parts and their libraries:
SparkFun: Released under the Creative Commons Attribution Share-Alike 3.0 License
SparkFun: http://creativecommons.org/licenses/by-sa/3.0
